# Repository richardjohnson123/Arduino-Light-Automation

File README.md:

# Arduino Light Automation
 An arduino circuit that automatically controls the lights using Kicad.

 PCB NOT TESTED

## Resources
 These resources served as the cornerstone this project:<br />

 * [Kicad basics](https://youtu.be/szu8dJoyikA?si=gNZHXsxOV4JxI1gA)<br />
 * [Arduino shield tutorial](https://youtu.be/ou_qRzNHZrw?si=L-_wdsPanHBMj-uL)<br />
 * [Arduino UNO R3 documentation](https://docs.arduino.cc/hardware/uno-rev3/)<br />

## Shield Dimensions
 The dimensions for the shield were verified using the Arduino UNO R3 datasheet:

## 3D PCB View

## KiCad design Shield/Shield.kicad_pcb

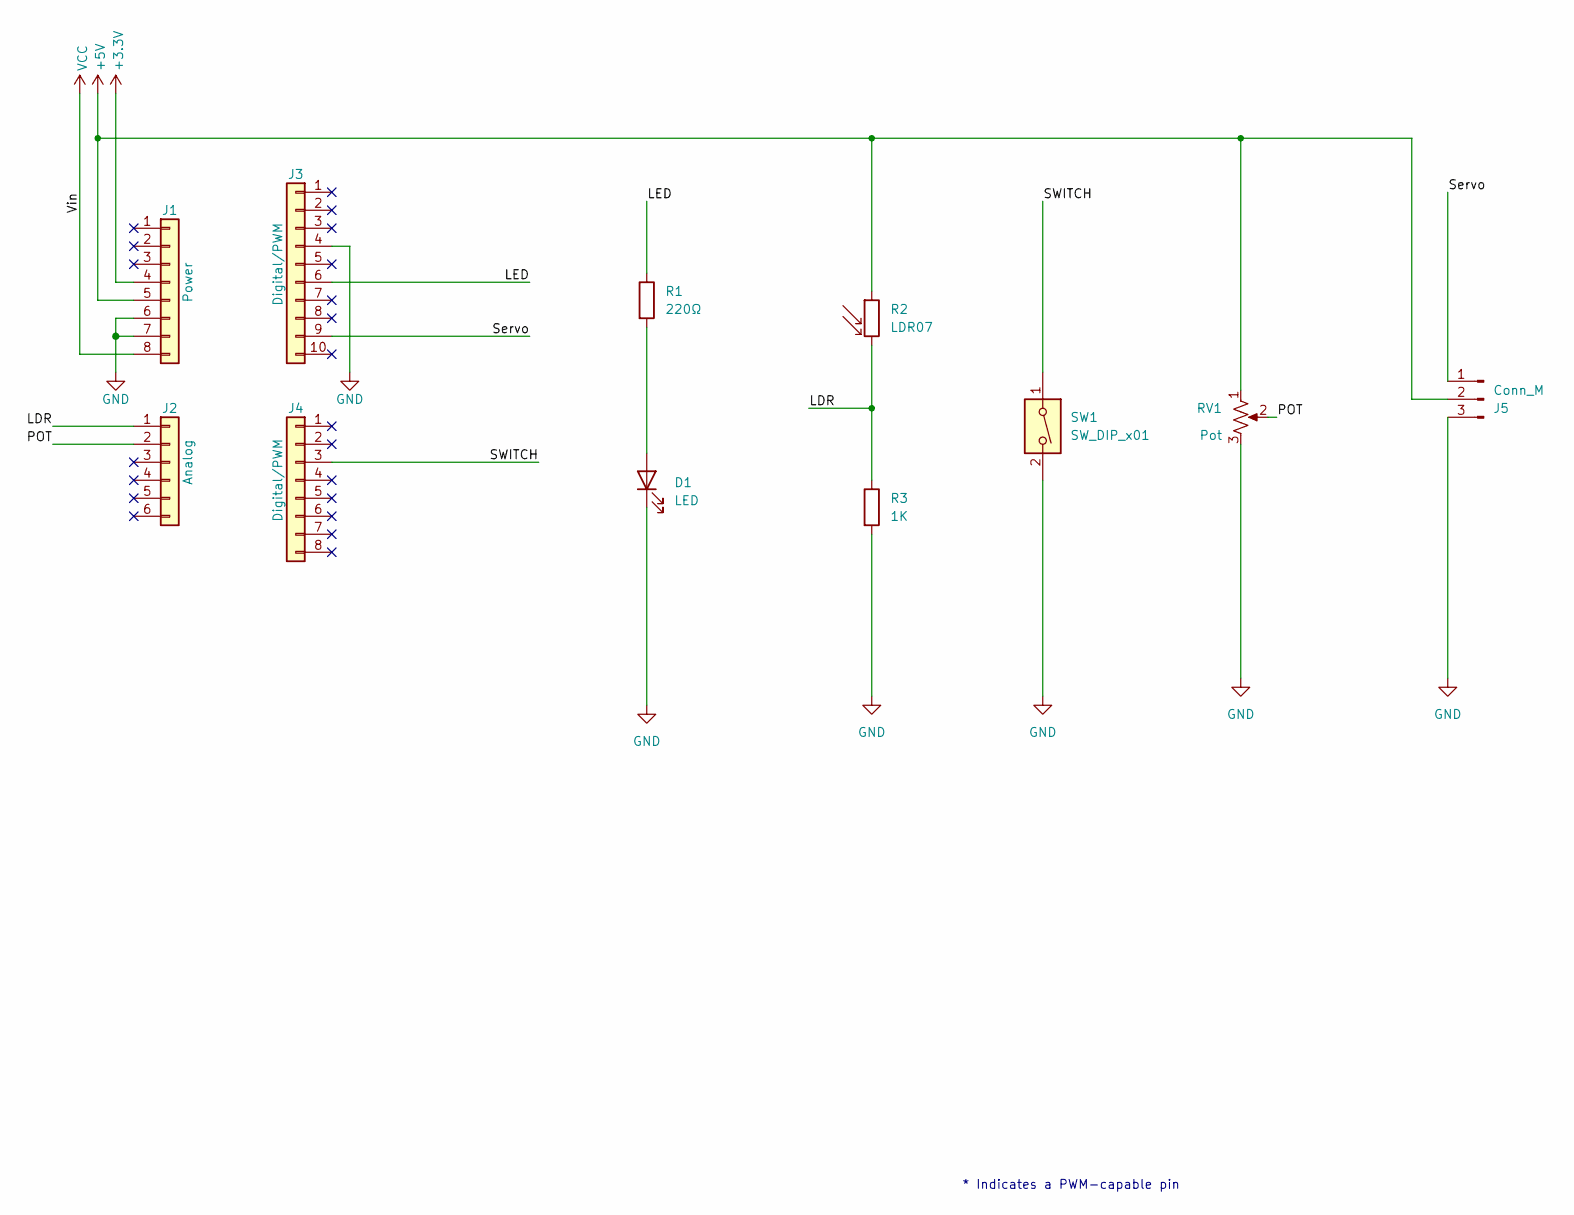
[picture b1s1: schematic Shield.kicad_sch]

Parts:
D1: LED; LED_D5.0mm_Clear
J1: Power; PinSocket_1x08_P2.54mm_Vertical
J2: Analog; PinSocket_1x06_P2.54mm_Vertical
J3: Digital/PWM; PinSocket_1x10_P2.54mm_Vertical
J4: Digital/PWM; PinSocket_1x08_P2.54mm_Vertical
J5: Conn_M; PinHeader_1x03_P2.54mm_Horizontal
R1: 220Ω; R_Axial_DIN0207_L6.3mm_D2.5mm_P15.24mm_Horizontal
R2: LDR07; R_LDR_5.1x4.3mm_P3.4mm_Vertical
R3: 1K; R_Axial_DIN0207_L6.3mm_D2.5mm_P15.24mm_Horizontal
RV1: Pot; Potentiometer_ACP_CA9-V10_Vertical
SW1: SW_DIP_x01; SW_DIP_SPSTx01_Slide_9.78x4.72mm_W7.62mm_P2.54mm

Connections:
+3V3: J1.4
+5V: J1.5, J5.2, R2.1, RV1.1
/LDR: J2.1, R2.2, R3.1
/LED: J3.6, R1.1
/POT: J2.2, RV1.2
/SWITCH: J4.3, SW1.1
/Servo: J3.9, J5.1
GND: D1.1 (K), J1.6, J1.7, J3.4, J5.3, R3.2, RV1.3, SW1.2
unnamed: D1.2 (A), R1.2
VCC: J1.8

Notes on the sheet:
* Indicates a PWM-capable pin

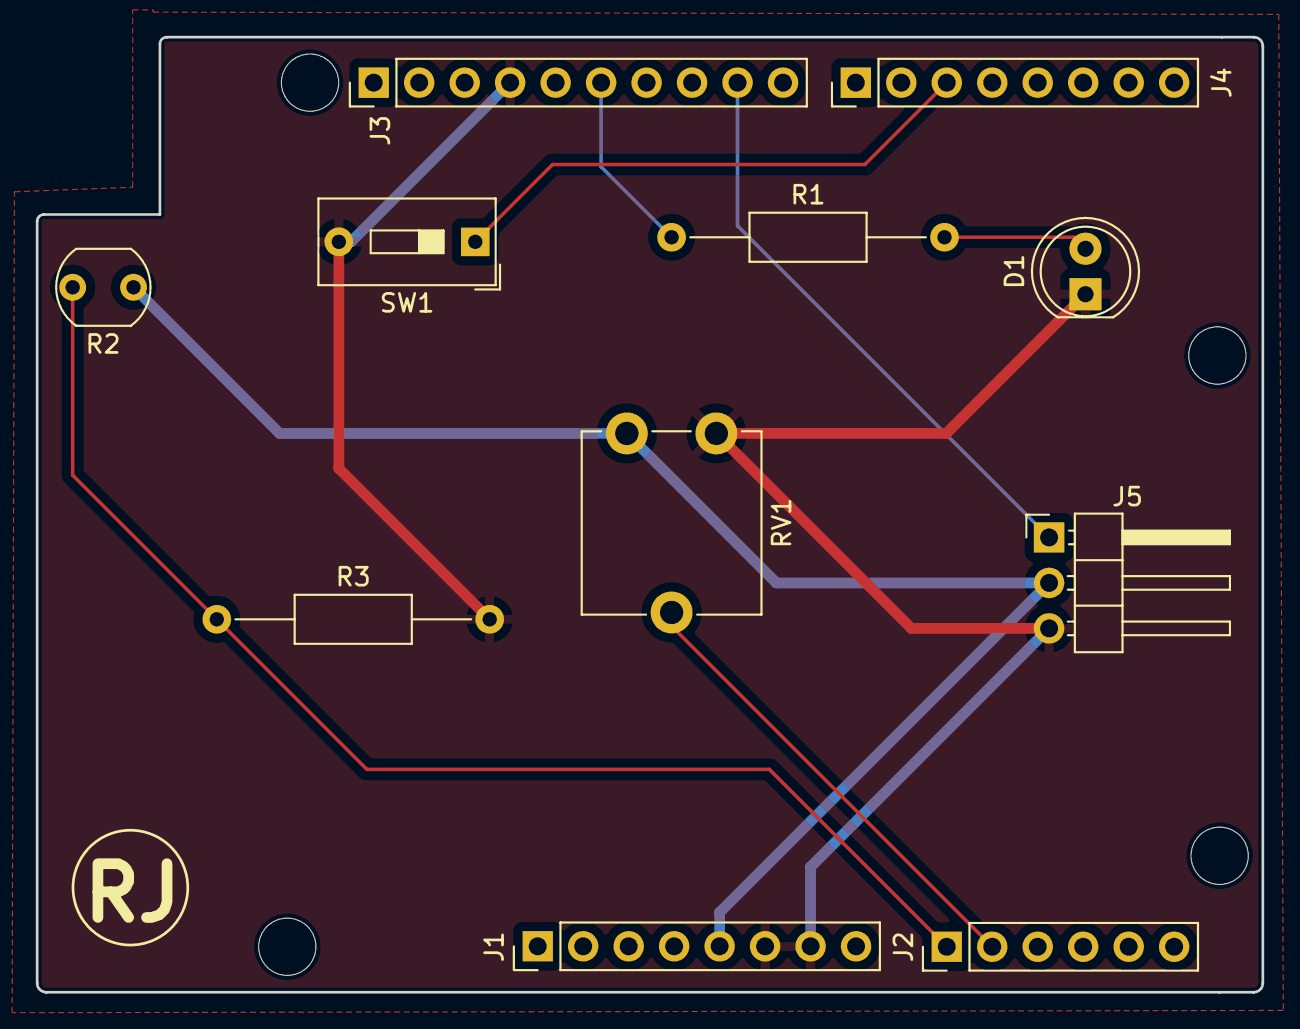
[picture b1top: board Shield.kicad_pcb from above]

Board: 2 copper layers, 68.5 x 53.3 mm, 15 parts (0 on the bottom side), 8 nets.

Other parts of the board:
MH1, MH2, MH3, MH3#2: MountingHole_3.2mm

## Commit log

2024-09-21 Kicad Shield Schematic
2024-09-21 Added Shield Files
2024-09-21 pushing
2024-09-21 testing
2024-09-21 Pushing Arduino Codes
2024-09-21 Adding Images
2024-09-24 New Edits
2024-09-24 Adding Changes
2024-09-24 Committing changes
2024-09-24 Organizing
2024-09-24 No Changes
